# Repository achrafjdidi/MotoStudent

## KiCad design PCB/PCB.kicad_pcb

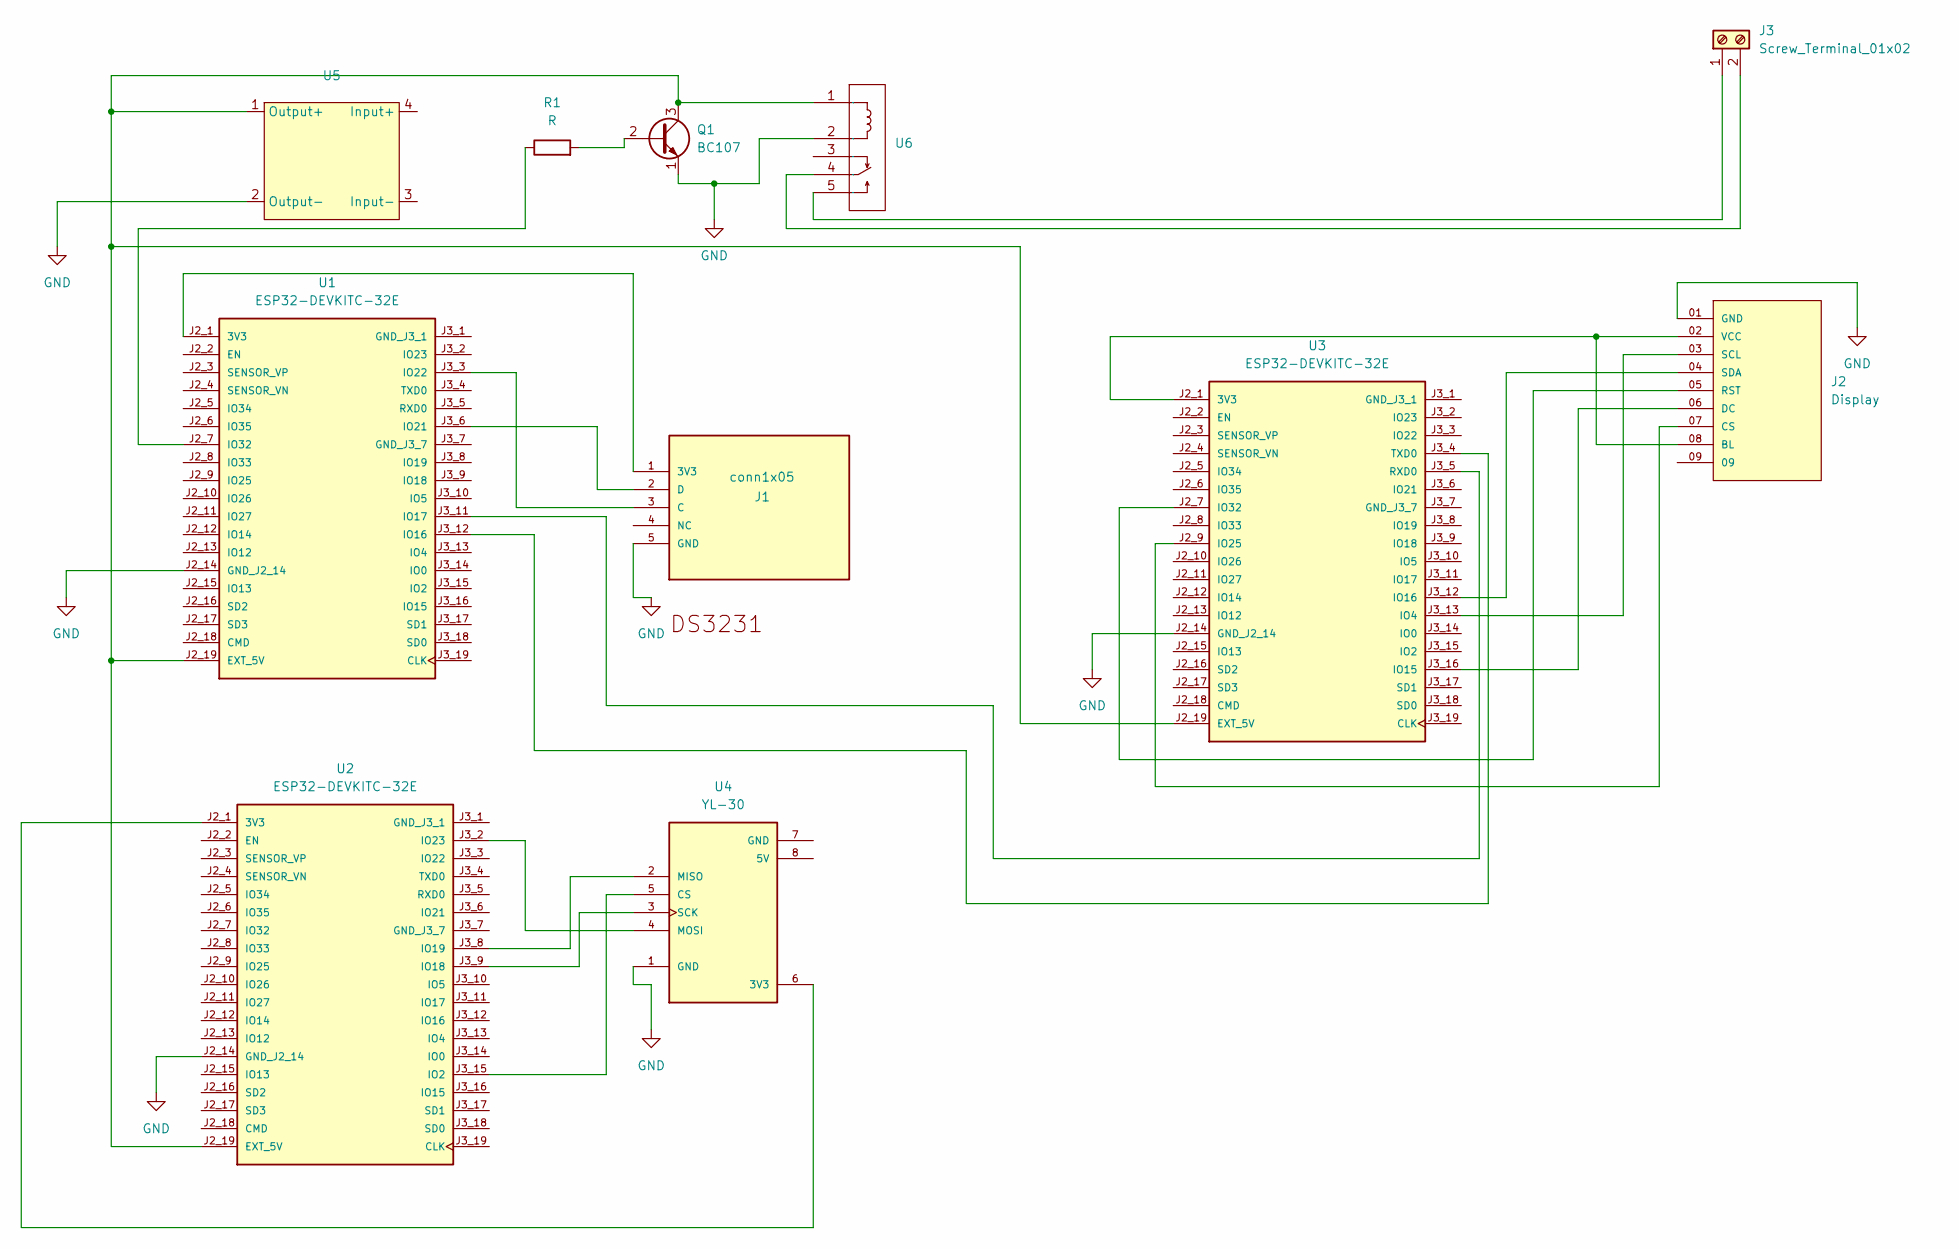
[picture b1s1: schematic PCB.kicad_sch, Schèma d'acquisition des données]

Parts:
J1: conn1x05; SAMTEC-DW-05-07-X-S-200
J2: Display; SAMTEC_ESQ-109-33-G-S; PARTREV R
J3: Screw_Terminal_01x02; TerminalBlock_Altech_AK300-2_P5.00mm
Q1: BC107; TO-18-3
R1: R; R_Axial_DIN0204_L3.6mm_D1.6mm_P5.08mm_Vertical
U1, U2, U3: ESP32-DEVKITC-32E; MODULE_ESP32-DEVKITC-32E; PARTREV 1.4
U4: YL-30; MODULE_254; PARTREV Jul 31, 2013
U5: LM25
U6: RELAY-TH_HF41F-X-ZS_C9900006963; Manufacturer Part HF41F/5-ZS; LCSC Part Name HF41F/5-ZS

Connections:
GND: J1.5 (GND), J2.01 (GND), Q1.1 (E), U1.J2_14 (GND_J2_14), U2.J2_14 (GND_J2_14), U3.J2_14 (GND_J2_14), U4.1 (GND), U5.2 (Output-), U6.2 (COIL)
unnamed: J1.1 (3V3), U1.J2_1 (3V3)
unnamed: J1.3 (C), U1.J3_3 (IO22)
unnamed: J1.2 (D), U1.J3_6 (IO21)
unnamed: J2.02 (VCC), J2.08 (BL), U3.J2_1 (3V3)
unnamed: J2.07 (CS), U3.J2_9 (IO25)
unnamed: J2.06 (DC), U3.J3_16 (IO15)
unnamed: J2.05 (RST), U3.J2_7 (IO32)
unnamed: J2.03 (SCL), U3.J3_13 (IO4)
unnamed: J2.04 (SDA), U3.J3_12 (IO16)
unnamed: J3.1, U6.5 (NO)
unnamed: J3.2, U6.4 (COM)
unnamed: Q1.2 (B), R1.2
unnamed: Q1.3 (C), U1.J2_19 (EXT_5V), U2.J2_19 (EXT_5V), U3.J2_19 (EXT_5V), U5.1 (Output+), U6.1 (COIL)
unnamed: U1.J3_12 (IO16), U3.J3_4 (TXD0)
unnamed: U1.J3_11 (IO17), U3.J3_5 (RXD0)
unnamed: R1.1, U1.J2_7 (IO32)
unnamed: U2.J2_1 (3V3), U4.6 (3V3)
unnamed: U2.J3_15 (IO2), U4.5 (CS)
unnamed: U2.J3_9 (IO18), U4.3 (SCK)
unnamed: U2.J3_8 (IO19), U4.2 (MISO)
unnamed: U2.J3_2 (IO23), U4.4 (MOSI)

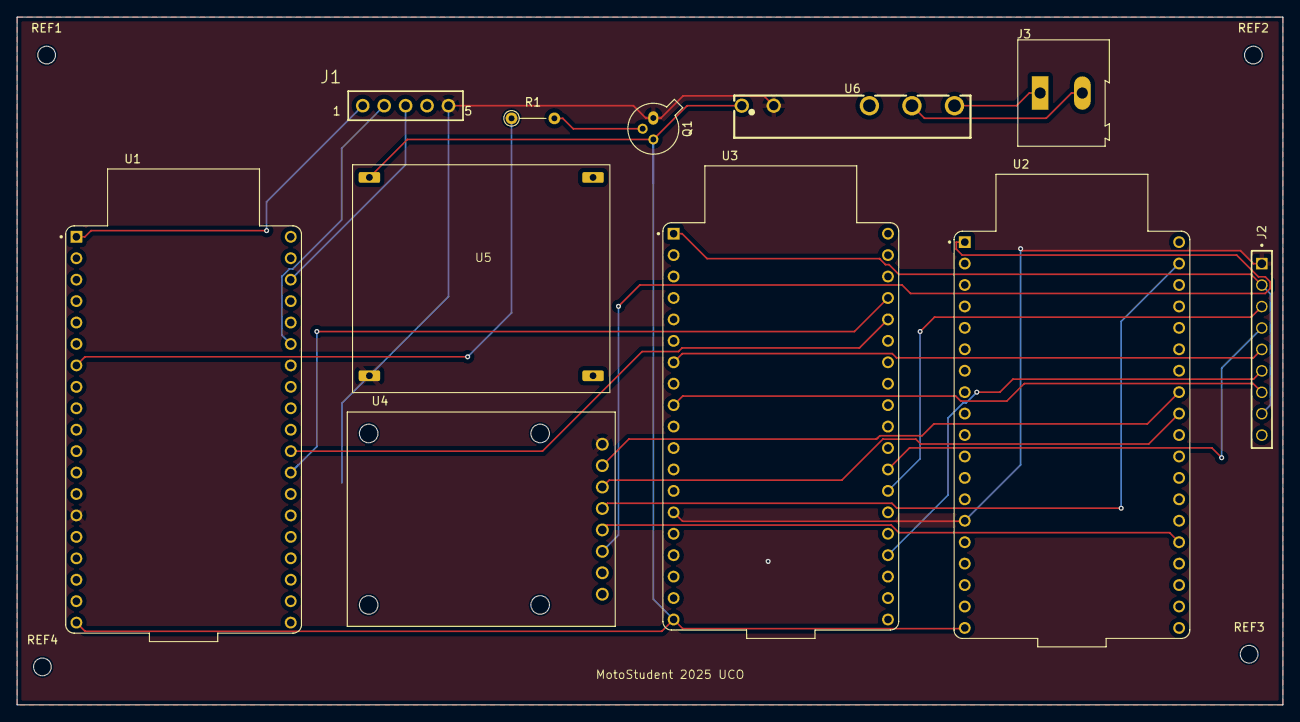
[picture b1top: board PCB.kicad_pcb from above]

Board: 2 copper layers, 150.0 x 81.5 mm, 15 parts (0 on the bottom side), 22 nets.

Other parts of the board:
REF1, REF2, REF3, REF4: MountingHole_2.1mm
